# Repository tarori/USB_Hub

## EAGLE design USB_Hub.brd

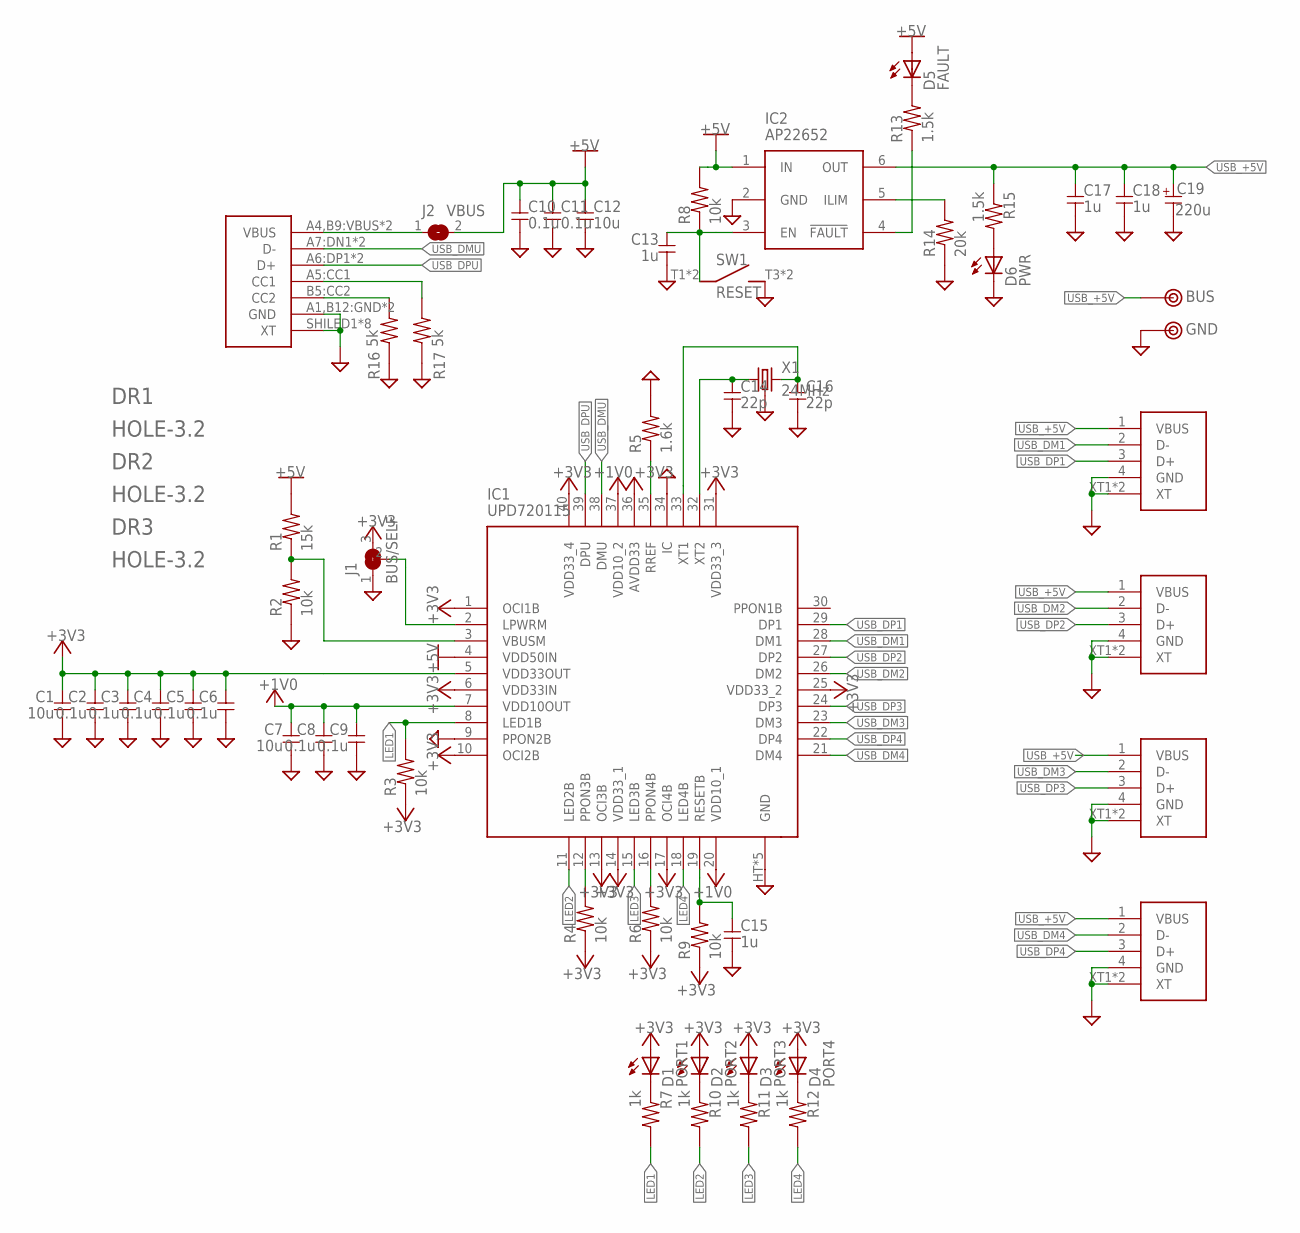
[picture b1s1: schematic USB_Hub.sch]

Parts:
C1, C7: 10u; 1608
C2, C3, C4, C5, C6, C8, C9, C10, C11: 0.1u; 1608
C12: 10u; 2012
C13, C15, C17, C18: 1u; 1608
C14, C16: 22p; 1608
C19: 220u; E2.5-6.5
CON1: USB-C; 5077CR-16-SMC2-BK-TR
CON2, CON3, CON4, CON5: USB-5075AR-04-WH; 5075AR-04-WH
D1: PORT1; LED2.5
D2: PORT2; LED2.5
D3: PORT3; LED2.5
D4: PORT4; LED2.5
D5: FAULT; D1608
D6: PWR; D1608
DR1, DR2, DR3: HOLE-3.2; HOLE_3.2
IC1: UPD720115; QFN40HT
IC2: AP22652; SOT23-6
J1: BUS/SELF; 1608-3-J
J2: VBUS; 1608-J
R1: 15k; 1608
R2, R3, R4, R6, R8, R9: 10k; 1608
R5: 1.6k; 1608
R7, R10, R11, R12: 1k; 1608
R13, R15: 1.5k; 1608
R14: 20k; 1608
R16, R17: 5k; 1608
SW1: RESET; SW_PUSH
TP1: BUS; TESTPIN
TP2: GND; TESTPIN
X1: 24MHz; KC3225

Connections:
+1V0: C7.1, C8.1, C9.1, IC1.7 (VDD10OUT), IC1.20 (VDD10_1), IC1.37 (VDD10_2)
+3V3: C1.1, C2.1, C3.1, C4.1, C5.1, C6.1, D1.A, D2.A, D3.A, D4.A, IC1.1 (OCI1B), IC1.5 (VDD33OUT), IC1.6 (VDD33IN), IC1.10 (OCI2B), IC1.13 (OCI3B), IC1.14 (VDD33_1), IC1.17 (OCI4B), IC1.25 (VDD33_2), IC1.31 (VDD33_3), IC1.36 (AVDD33), IC1.40 (VDD33_4), J1.3, R3.1, R4.1, R6.1, R9.1
+5V: C10.1, C11.1, C12.1, D5.A, IC1.4 (VDD50IN), IC2.1 (IN), J2.2, R1.2, R8.2
GND: C1.2, C2.2, C3.2, C4.2, C5.2, C6.2, C7.2, C8.2, C9.2, C10.2, C11.2, C12.2, C13.2, C14.2, C15.2, C16.2, C17.2, C18.2, C19.- (2), CON1.A1,B12:GND (GND), CON1.B1,A12:GND (GND), CON1.SHILED1 (XT), CON1.SHILED2 (XT), CON1.SHILED3 (XT), CON1.SHILED4 (XT), CON1.SHILED5 (XT), CON1.SHILED6 (XT), CON1.SHILED7 (XT), CON1.SHILED8 (XT), CON2.4 (GND), CON2.XT1 (XT), CON2.XT2 (XT), CON3.4 (GND), CON3.XT1 (XT), CON3.XT2 (XT), CON4.4 (GND), CON4.XT1 (XT), CON4.XT2 (XT), CON5.4 (GND), CON5.XT1 (XT), CON5.XT2 (XT), D6.K, IC1.9 (PPON2B), IC1.34 (IC), IC1.HT (GND), IC1.HT1 (GND), IC1.HT2 (GND), IC1.HT3 (GND), IC1.HT4 (GND), IC2.2 (GND), J1.1, R2.1, R5.2, R14.1, R16.1, R17.1, SW1.T3 (2), SW1.T4 (2), TP2.1, X1.2 (GND), X1.4 (GND)
LED1: IC1.8 (LED1B), R3.2, R7.2
LED2: IC1.11 (LED2B), R10.2
LED3: IC1.15 (LED3B), R11.2
LED4: IC1.18 (LED4B), R12.2
unnamed: CON1.A4,B9:VBUS (VBUS), CON1.B4,A9:VBUS (VBUS), J2.1
unnamed: D5.K, R13.2
unnamed: IC1.3 (VBUSM), R1.1, R2.2
unnamed: IC1.35 (RREF), R5.1
unnamed: C14.1, IC1.32 (XT2), X1.1
unnamed: C16.1, IC1.33 (XT1), X1.3 (2)
unnamed: C15.1, IC1.19 (RESETB), R9.2
unnamed: D1.K, R7.1
unnamed: D2.K, R10.1
unnamed: D3.K, R11.1
unnamed: D4.K, R12.1
unnamed: IC2.4 (!FAULT), R13.1
unnamed: IC2.5 (ILIM), R14.2
unnamed: IC1.16 (PPON4B), R6.2
unnamed: IC1.12 (PPON3B), R4.2
unnamed: D6.A, R15.2
unnamed: IC1.2 (LPWRM), J1.2
unnamed: CON1.B5:CC2 (CC2), R16.2
unnamed: CON1.A5:CC1 (CC1), R17.2
USB_+5V: C17.1, C18.1, C19.+ (1), CON2.1 (VBUS), CON3.1 (VBUS), CON4.1 (VBUS), CON5.1 (VBUS), IC2.6 (OUT), R15.1, TP1.1
USB_DM1: CON2.2 (D-), IC1.28 (DM1)
USB_DM2: CON3.2 (D-), IC1.26 (DM2)
USB_DM3: CON4.2 (D-), IC1.23 (DM3)
USB_DM4: CON5.2 (D-), IC1.21 (DM4)
USB_DMU: CON1.A7:DN1 (D-), CON1.B7:DN2 (D-), IC1.38 (DMU)
USB_DP1: CON2.3 (D+), IC1.29 (DP1)
USB_DP2: CON3.3 (D+), IC1.27 (DP2)
USB_DP3: CON4.3 (D+), IC1.24 (DP3)
USB_DP4: CON5.3 (D+), IC1.22 (DP4)
USB_DPU: CON1.A6:DP1 (D+), CON1.B6:DP2 (D+), IC1.39 (DPU)
VBUS_EN: C13.1, IC2.3 (EN), R8.1, SW1.T1 (1), SW1.T2 (1)

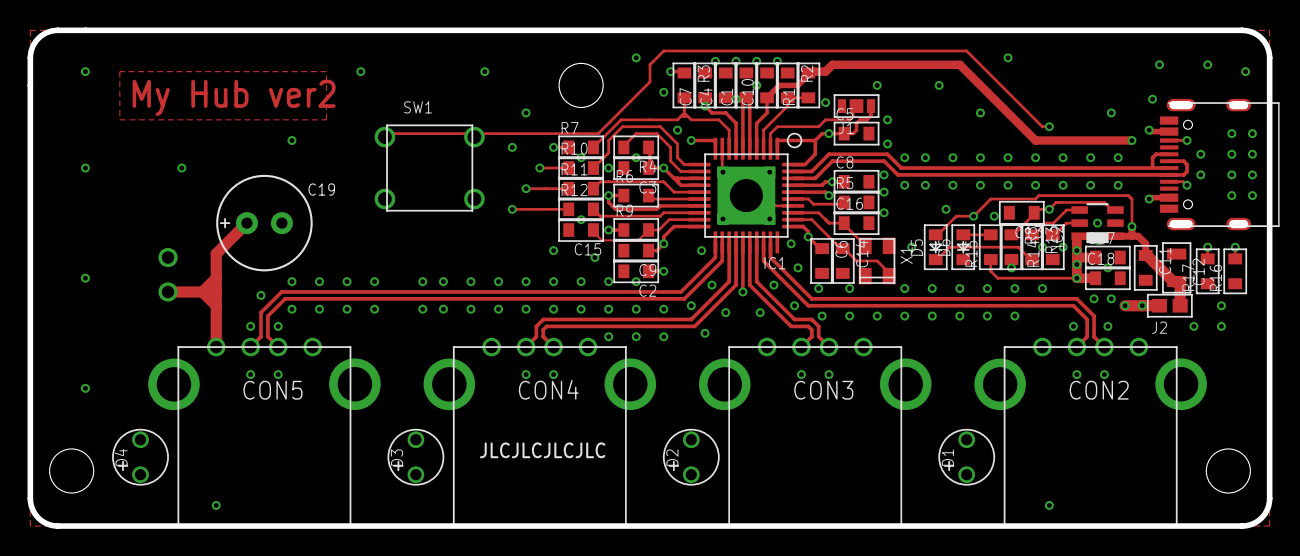
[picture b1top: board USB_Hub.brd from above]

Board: 4 copper layers, 90.0 x 36.0 mm, 58 parts (0 on the bottom side), 39 nets.

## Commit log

2023-07-29 ver1
2023-08-25 電圧確認用のポートを追加
2023-08-25 写真を追加
2024-06-15 Type-Cに変更
